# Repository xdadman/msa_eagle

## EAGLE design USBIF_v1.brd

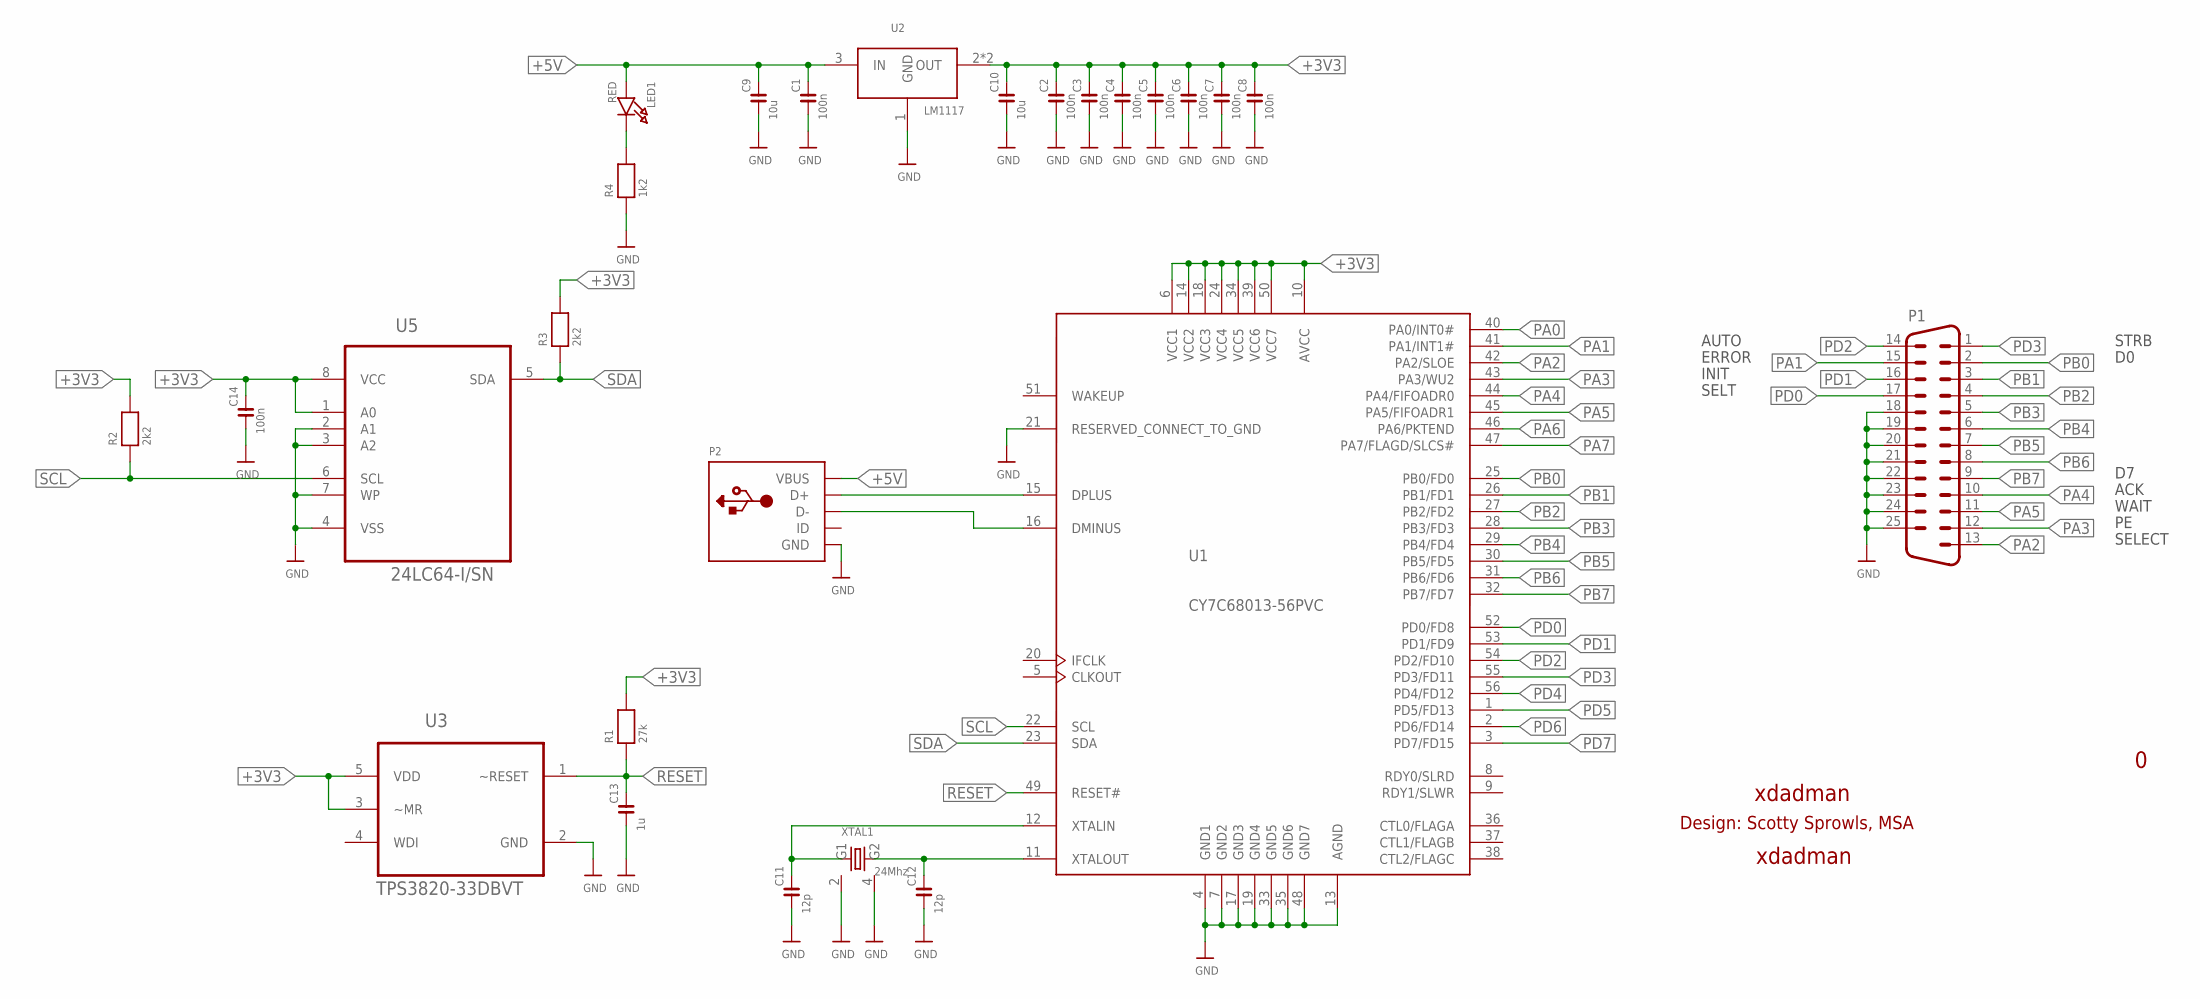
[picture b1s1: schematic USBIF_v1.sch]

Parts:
C1: 100n; C0805
C2, C3, C4, C5, C6, C7, C8, C14: 100n; C0603
C9, C10: 10u; C1206
C11, C12: 12p; C0603
C13: 1u; C0805
LED1: RED; CHIPLED_0603
P1: M25D
P2: USBMINIBLARGE; USB-MINIB_LARGER
R1: 27k; R0805
R2, R3: 2k2; R0805
R4: 1k2; R0805
U1: CY7C68013-56PVC; SSOP-56
U2: LM1117; SOT223
U3: TPS3820-33DBVT; SOT95P280X145-5N
U5: 24LC64-I/SN; SOIC127P600X175-8N_JDA2
XTAL1: 24Mhz; AKER_7X5

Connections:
+3V3: C2.2, C3.2, C4.2, C5.2, C6.2, C7.2, C8.2, C10.2, C14.2, R1.2, R2.2, R3.2, U1.6 (VCC1), U1.10 (AVCC), U1.14 (VCC2), U1.18 (VCC3), U1.24 (VCC4), U1.34 (VCC5), U1.39 (VCC6), U1.50 (VCC7), U2.2 (OUT), U2.4 (OUT), U3.3 (~MR), U3.5 (VDD), U5.1 (A0), U5.8 (VCC)
+5V: C1.2, C9.2, LED1.A, P2.VBUS, U2.3 (IN)
GND: C1.1, C2.1, C3.1, C4.1, C5.1, C6.1, C7.1, C8.1, C9.1, C10.1, C11.1, C12.1, C13.1, C14.1, P1.18, P1.19, P1.20, P1.21, P1.22, P1.23, P1.24, P1.25, P2.GND, R4.1, U1.4 (GND1), U1.7 (GND2), U1.13 (AGND), U1.17 (GND3), U1.19 (GND4), U1.21 (RESERVED_CONNECT_TO_GND), U1.33 (GND5), U1.35 (GND6), U1.48 (GND7), U2.1 (GND), U3.2 (GND), U5.2 (A1), U5.3 (A2), U5.4 (VSS), U5.7 (WP), XTAL1.2 (G1), XTAL1.4 (G2)
unnamed: P2.D+, U1.15 (DPLUS)
unnamed: P2.D-, U1.16 (DMINUS)
unnamed: LED1.C, R4.2
unnamed: C12.2, U1.11 (XTALOUT), XTAL1.3 (S2)
unnamed: C11.2, U1.12 (XTALIN), XTAL1.1 (S1)
PA0: U1.40 (PA0/INT0#)
PA1: P1.15, U1.41 (PA1/INT1#)
PA2: P1.13, U1.42 (PA2/SLOE)
PA3: P1.12, U1.43 (PA3/WU2)
PA4: P1.10, U1.44 (PA4/FIFOADR0)
PA5: P1.11, U1.45 (PA5/FIFOADR1)
PA6: U1.46 (PA6/PKTEND)
PA7: U1.47 (PA7/FLAGD/SLCS#)
PB0: P1.2, U1.25 (PB0/FD0)
PB1: P1.3, U1.26 (PB1/FD1)
PB2: P1.4, U1.27 (PB2/FD2)
PB3: P1.5, U1.28 (PB3/FD3)
PB4: P1.6, U1.29 (PB4/FD4)
PB5: P1.7, U1.30 (PB5/FD5)
PB6: P1.8, U1.31 (PB6/FD6)
PB7: P1.9, U1.32 (PB7/FD7)
PD0: P1.17, U1.52 (PD0/FD8)
PD1: P1.16, U1.53 (PD1/FD9)
PD2: P1.14, U1.54 (PD2/FD10)
PD3: P1.1, U1.55 (PD3/FD11)
PD4: U1.56 (PD4/FD12)
PD5: U1.1 (PD5/FD13)
PD6: U1.2 (PD6/FD14)
PD7: U1.3 (PD7/FD15)
RESET: C13.2, R1.1, U1.49 (RESET#), U3.1 (~RESET)
SCL: R2.1, U1.22 (SCL), U5.6 (SCL)
SDA: R3.1, U1.23 (SDA), U5.5 (SDA)

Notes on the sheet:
STRB
SELT
INIT
AUTO
ERROR
SELECT
ACK
WAIT
xdadman
Design: Scotty Sprowls, MSA

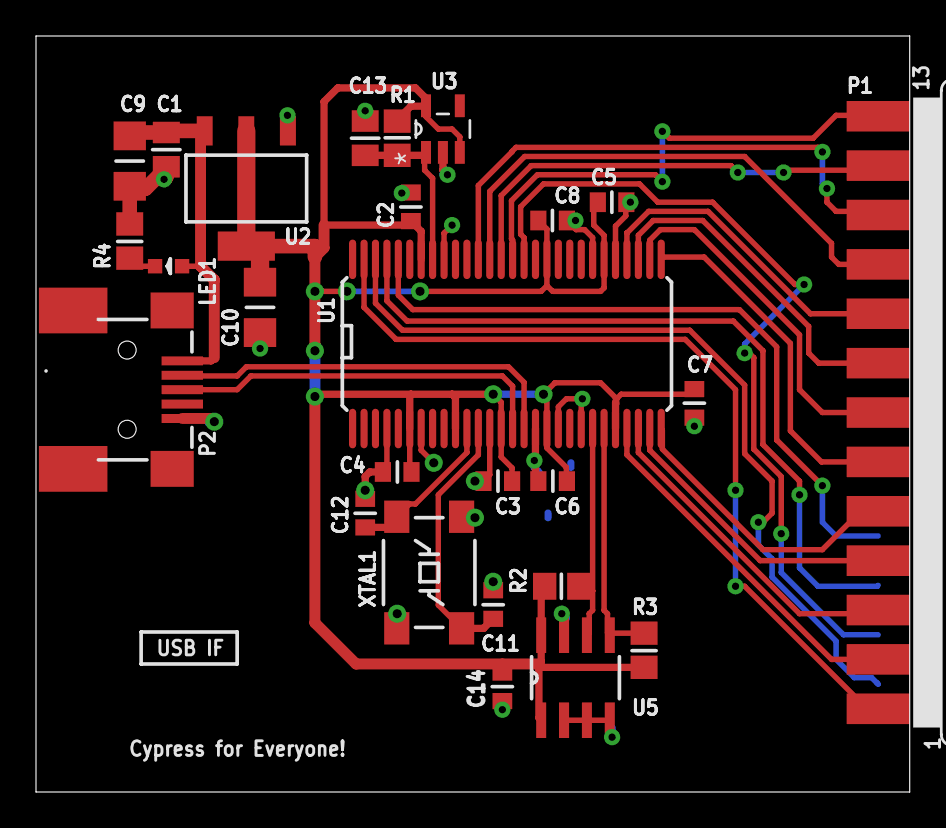
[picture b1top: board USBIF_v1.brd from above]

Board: 2 copper layers, 48.5 x 42.0 mm, 26 parts (0 on the bottom side), 28 nets.
